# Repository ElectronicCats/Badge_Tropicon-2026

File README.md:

# Badge Tropicon 2026

Badge Oficial de Trpicon 2026

## Hardware
- ESP32-C6
- AHT30
- SI4463
- VGdd79S915N0S1
- Wide Angle 2.79 inch 142x428 Color IPS TFT Display NV3007 Controller

## Tecnologia
- LoRa
- WIFi
- BLE
- Zigbee
- Thread
- [AIS](https://es.wikipedia.org/wiki/Sistema_de_Identificaci%C3%B3n_Autom%C3%A1tica)
- [meshtastic](https://github.com/meshtastic)

<div align="center" markdown="1">

<h1>Tropicon 2026 — Firmware</h1>

Firmware personalizado de Meshtastic para el badge del evento **Tropicon 2026**, desarrollado por **Electronic Cats**. Incluye integración de agenda de pláticas, talleres, monitor AIS de embarcaciones, telemetría ambiental y mensajería LoRa.

</div>

## Primeros pasos
> [!IMPORTANT]
> INSTRUCCIONES COMPLETAS DE USO

Dirigete al [Repositorio de Fimrware](https://github.com/ElectronicCats/Tropicon-2026_Firmware) para instrucciones completas de uso

## Botones y navegación general

El badge cuenta con cuatro botones físicos:

| Botón | Pulsación corta | Pulsación larga (~1 s) |
|-------|----------------|------------------------|
| **UP** | Pantalla anterior / Ítem anterior | Abrir menú de acciones de la pantalla actual |
| **DOWN** | Pantalla siguiente / Ítem siguiente | — |
| **LEFT** | Izquierda / Día anterior (en Talks) | — |
| **RIGHT** | Derecha / Siguiente stage (en Talks) | — |

> [!TIP]
> El **botón UP largo** es la acción principal de cada pantalla. Desde cualquier pantalla, úsalo para acceder a las opciones disponibles: enviar mensajes, navegar a la agenda, configurar LoRa, etc.

---

## Pantallas del dispositivo

Navega entre pantallas con **UP** (anterior) y **DOWN** (siguiente). El ciclo completo es:

| # | Pantalla | Descripción |
|---|----------|-------------|
| 1 | **Talks** | Agenda de pláticas y talleres de Tropicon 2026 |
| 2 | **AIS** | Monitor de embarcaciones (Automatic Identification System) |
| 3 | **Clock** | Reloj digital o analógico |
| 4 | **Home** | Estado del nodo: nombre, batería y canal LoRa |
| 5 | **Messages** | Mensajes de texto recibidos y enviados en la malla LoRa |
| 6 | **Node List** | Lista de nodos detectados en la malla |
| 7 | **Telemetry** | Métricas del entorno: Temperatura y Humedad (sensor AHT10) |
| 8 | **GPS** | Brújula y coordenadas (deshabilitado — sin módulo GPS) |
| 9 | **LoRa** | Estadísticas de radio: SNR, RSSI y frecuencia |
| 10 | **System** | Información de sistema: uptime y memoria libre |

---

## Menú de Acciones (Home Action)

Desde la pantalla **Home**, presiona **UP largo** para abrir el menú *"Home Action"*:

| Opción | Qué hace |
|--------|----------|
| **Back** | Cierra el menú sin cambios |
| **Sleep Screen** | Apaga la pantalla para ahorrar batería (cualquier botón la reactiva) |
| **Talks** | Abre directamente la agenda de pláticas y talleres |

---

## Agenda de Pláticas y Talleres (Talks)

La agenda carga automáticamente los datos desde la flash del dispositivo:

| Archivo | Contenido |
|---------|-----------|
| `/schedule.json` | Pláticas principales (Track 1 y Track Villas) |
| `/talleres.json` | Talleres simultáneos (Salón Maya, La Isla, Suite 1, Suite 2) |

Para acceder a la agenda puedes:
- Navegar con **UP/DOWN** hasta llegar a la pantalla **Talks**, o
- Desde cualquier pantalla, abrir el menú con **UP largo** y seleccionar **Talks**.

### Vista lista

Muestra el listado de pláticas del día y stage (escenario) actualmente seleccionados. El encabezado indica `Día — Stage`.

| Acción | Resultado |
|--------|-----------|
| **UP** corto | Sube al ítem anterior de la lista |
| **UP** corto (en la primera plática) | Sale de la agenda y regresa al menú principal |
| **DOWN** | Baja al ítem siguiente de la lista |
| **LEFT** | Cambia al día anterior (cíclico); resetea el stage y la selección |
| **RIGHT** | Avanza al siguiente stage; si ya es el último stage, avanza al siguiente día |
| **UP largo** | Entra a la **vista detalle** de la plática seleccionada |

> [!TIP]
> Para **salir de la agenda en cualquier momento**, presiona **UP** cuando estés en la primera plática de la lista — el badge regresará automáticamente al menú principal de pantallas.

### Vista detalle

Muestra el título completo, nombre del ponente, horario, sala, imagen del ponente y el marcador de interés actual.

| Acción | Resultado |
|--------|-----------|
| **UP** corto | Regresa a la vista lista |
| **DOWN** | Avanza a la siguiente plática (permanece en vista detalle) |
| **LEFT** | Retrocede a la plática anterior (cambia de stage/día si es necesario) |
| **RIGHT** | Avanza a la plática siguiente (cambia de stage/día si es necesario) |
| **UP largo** | Cicla el estado de interés: `Sin interés → Asistir → Tal vez → Saltar` |

### Marcadores de interés y notificaciones

Los marcadores se muestran en la esquina superior derecha de cada plática en la vista lista:

| Marcador | Estado | Descripción |
|----------|--------|-------------|
| _(vacío)_ | Sin interés | Sin acción |
| `[A]` | **Asistir** | El badge enviará una notificación a tu app Meshtastic 10 minutos antes de que comience |
| `[T]` | **Tal vez** | Recordatorio opcional |
| `[S]` | **Saltar** | Marcado para no asistir |

> [!IMPORTANT]
> Los marcadores se guardan automáticamente en la flash del dispositivo y **persisten entre reinicios**. Si tienes el badge conectado a la app Meshtastic y una plática marcada como `[A]` (Asistir) está por comenzar, recibirás una notificación push en tu teléfono con el mensaje _"Tropicon: [nombre de plática] empieza en 10 min"_.

---

## Monitor AIS de Embarcaciones

La pantalla **AIS** recibe y decodifica señales VHF del sistema de identificación automática de embarcaciones (AIS), usado internacionalmente por barcos para reportar su posición y datos.

Para acceder, navega con **UP/DOWN** hasta la pantalla **AIS**.

### Información mostrada

La pantalla se divide en:

- **Encabezado**: muestra el canal AIS activo (`ch A` o `ch B`, es decir canal 87B o 88B) y el total de tramas recibidas (`frm`).
- **Lista de embarcaciones** (ordenadas de más reciente a más antigua): cada fila contiene:
  - **MMSI**: identificador único de la embarcación (9 dígitos)
  - **RSSI**: nivel de señal recibida en dBm
  - **Antigüedad**: tiempo desde la última trama recibida (en segundos, o `>1h`)
  - **Tipo de mensaje**: badge `T1`, `T2`, etc. (tipo de trama AIS)
  - **Sentencia NMEA**: frase AIS cruda recibida (truncada para caber en pantalla)

Cuando no se han recibido embarcaciones, la pantalla muestra `Listening...` indicando que el receptor está activo y esperando señales.

> [!NOTE]
> El AIS trabaja en frecuencias VHF (~162 MHz). La recepción depende de la proximidad a cuerpos de agua navegables y de la línea de visión con las embarcaciones.

---

## Mensajes — Recibir y Enviar

La pantalla **Messages** muestra todos los mensajes de texto intercambiados en la malla LoRa, presentados en formato de burbuja (mensajes propios a la derecha, mensajes recibidos a la izquierda).

### Navegar a la pantalla de mensajes

Usa **RIGHT/LEFT** desde cualquier pantalla hasta llegar a **Messages**.

### Ver mensajes

- Cada mensaje muestra: remitente, tiempo transcurrido, canal o DM, y el texto.
- Los mensajes propios muestran un indicador de estado de entrega:
  - Palomita `✓` — mensaje confirmado (ACK del destino)
  - `✗` — falla o tiempo de espera agotado
  - Círculo — reenviado por un nodo relay

### Enviar un mensaje (nuevo)

1. Navega a la pantalla **Messages**.
2. Presiona **UP largo** para abrir el menú *"Message Action"*.
3. Selecciona **Reply** → **With Preset** para elegir un mensaje predefinido de la lista.
4. Usa **RIGHT/LEFT** para seleccionar el mensaje deseado y **UP largo** para enviarlo.

> [!NOTE]
> La opción **With Freetext** (teclado libre) solo aparece si se detecta un teclado externo conectado al badge.

### Responder a un mensaje recibido

1. Navega a la pantalla **Messages** donde aparece el mensaje.
2. Presiona **UP largo** para abrir *"Message Action"*.
3. Selecciona **Reply** y elige:
   - **With Preset** — selecciona una respuesta de la lista de mensajes predefinidos.
   - **With Freetext** — escribe tu propio texto (requiere teclado externo).

### Otras opciones del menú Message Action

| Opción | Qué hace |
|--------|----------|
| **Back** | Cierra el menú |
| **Reply** | Abre el submenú para responder |
| **View Chats** | Cambia el filtro de vista: todos los mensajes, por canal o por conversación directa |
| **Mute Channel** / **Unmute Channel** | Silencia o reactiva las notificaciones del canal actual |
| **Delete** | Elimina mensajes (el más antiguo, el actual o todos) |

---

## Telemetría del Entorno

La pantalla **Telemetry** muestra las métricas ambientales medidas en tiempo real por el sensor **AHT10** integrado en el badge:

- **Temperatura** en grados Celsius
- **Humedad relativa** en porcentaje (%)

Para acceder, navega con **UP/DOWN** hasta llegar a la pantalla **Telemetry**.

Las métricas se actualizan automáticamente cada segundo. El badge también transmite estos datos periódicamente por la malla LoRa para que otros nodos y la app Meshtastic puedan visualizarlos.

---

### Recursos útiles

- [Documentación oficial de Meshtastic](https://meshtastic.org/docs/) — arquitectura, módulos, protocolo LoRa y API.
- [Repositorio base de Meshtastic firmware](https://github.com/meshtastic/firmware) — código fuente upstream del que se deriva este firmware.
- [Documentación de PlatformIO](https://docs.platformio.org/) — comandos de compilación, ambientes y gestión de librerías.
- [Foro de la comunidad Meshtastic](https://meshtastic.discourse.group/) — preguntas, proyectos y soporte comunitario.
- [Electronic Cats en GitHub](https://github.com/ElectronicCats) — otros proyectos de hardware y firmware de Electronic Cats.

## Credits

Designed and developed by the **Electronic Cats** firmware and hardware team.

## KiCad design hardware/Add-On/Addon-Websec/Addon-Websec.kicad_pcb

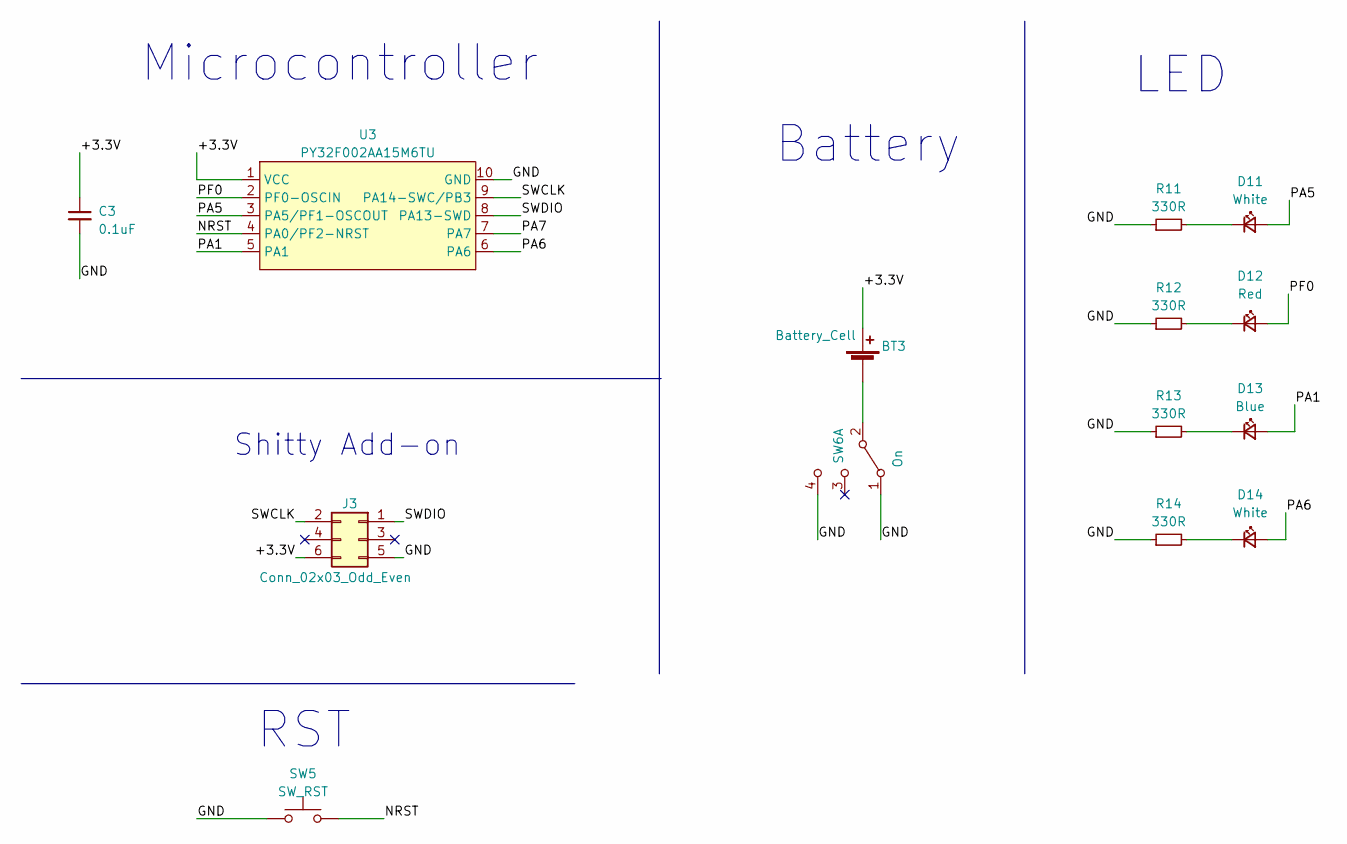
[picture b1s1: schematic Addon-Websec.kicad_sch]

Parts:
BT3: Battery_Cell; BAT-HLD-001; LCSC# C964833
C3: 0.1uF; C_0805_2012Metric; LCSC# C235731
D11, D14: White; LED_0805_2012Metric; LCSC# C84258
D12: Red; LED_0805_2012Metric; LCSC# C965812
D13: Blue; LED_0805_2012Metric; LCSC# C205441
J3: Conn_02x03_Odd_Even; B-2100N06P-B111_CKM; LCSC# C124390
R11, R12, R13, R14: 330R; R_0805_2012Metric; LCSC# C119075
SW5: SW_RST; SW_SPST_TL3342; LCSC# C318889
SW6: On; MSK12C02; LCSC# C431540
U3: PY32F002AA15M6TU; PY32F002AA15M; LCSC# C5292058

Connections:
/+3.3V: BT3.2 (+), C3.1, J3.6, U3.1 (VCC)
/GND: C3.2, J3.5, R11.1, R12.1, R13.1, R14.1, SW5.1, SW6.1 (A), SW6.4 (C), U3.10 (GND)
/NRST: SW5.2, U3.4 (PA0/PF2-NRST)
/PA1: D13.2 (A), U3.5 (PA1)
/PA5: D11.2 (A), U3.3 (PA5/PF1-OSCOUT)
/PA6: D14.2 (A), U3.6 (PA6)
/PA7: U3.7 (PA7)
/PF0: D12.2 (A), U3.2 (PF0-OSCIN)
/SWCLK: J3.2, U3.9 (PA14-SWC/PB3)
/SWDIO: J3.1, U3.8 (PA13-SWD)
unnamed: BT3.1 (-), SW6.2 (B)
unnamed: D11.1 (K), R11.2
unnamed: D12.1 (K), R12.2
unnamed: D13.1 (K), R13.2
unnamed: D14.1 (K), R14.2

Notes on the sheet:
Battery
RST
Microcontroller
Shitty Add-on
LED

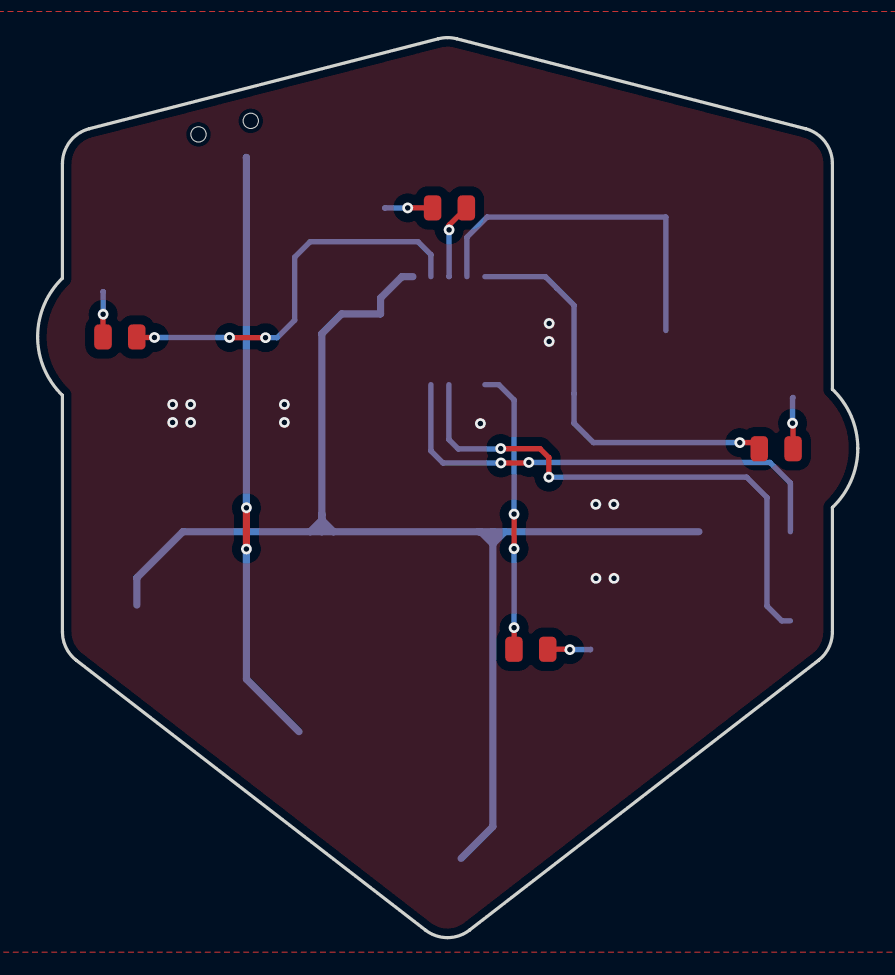
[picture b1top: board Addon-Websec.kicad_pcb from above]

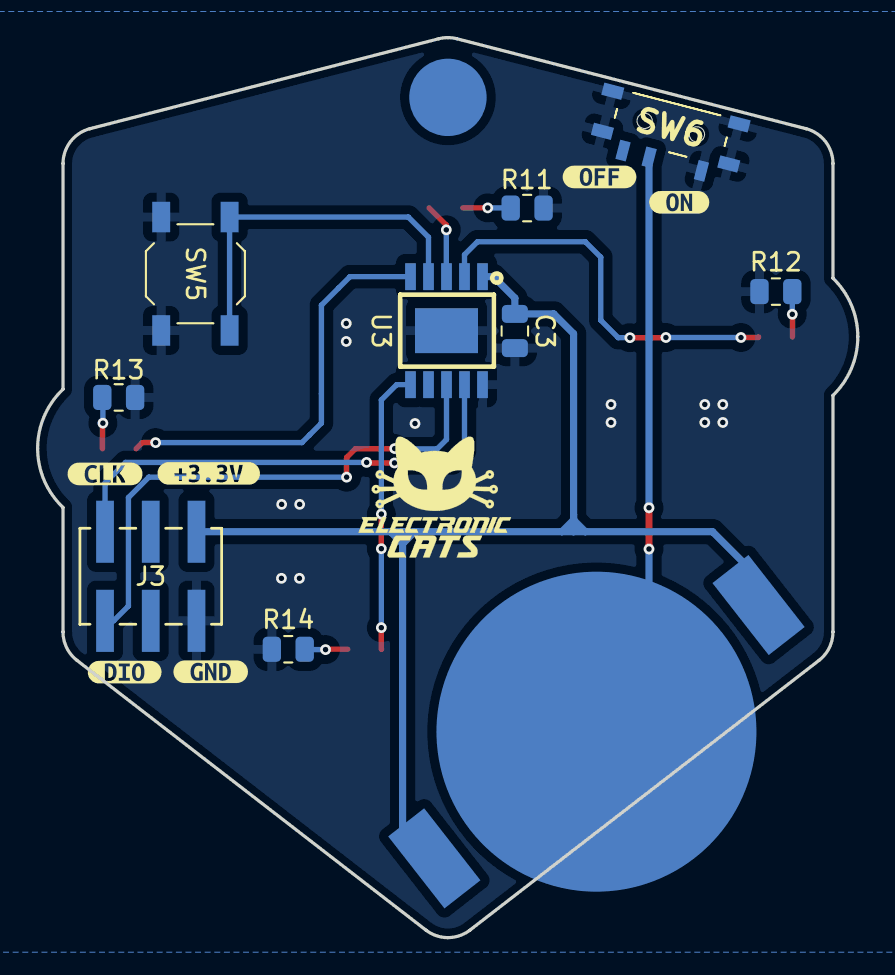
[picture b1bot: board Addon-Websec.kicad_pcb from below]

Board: 2 copper layers, 45.6 x 50.0 mm, 20 parts (16 on the bottom side), 14 nets.

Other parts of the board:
kibuzzard-66EC9C8E: G***; kibuzzard-66EC9C8E
kibuzzard-66EC9CA5: G***; kibuzzard-66EC9CA5
kibuzzard-66EC9D2A: G***; kibuzzard-66EC9D2A
kibuzzard-66EC9DE2: G***; kibuzzard-66EC9DE2
kibuzzard-66ECA9F9: G***; kibuzzard-66ECA9F9
kibuzzard-66ECAA39: G***; kibuzzard-66ECAA39

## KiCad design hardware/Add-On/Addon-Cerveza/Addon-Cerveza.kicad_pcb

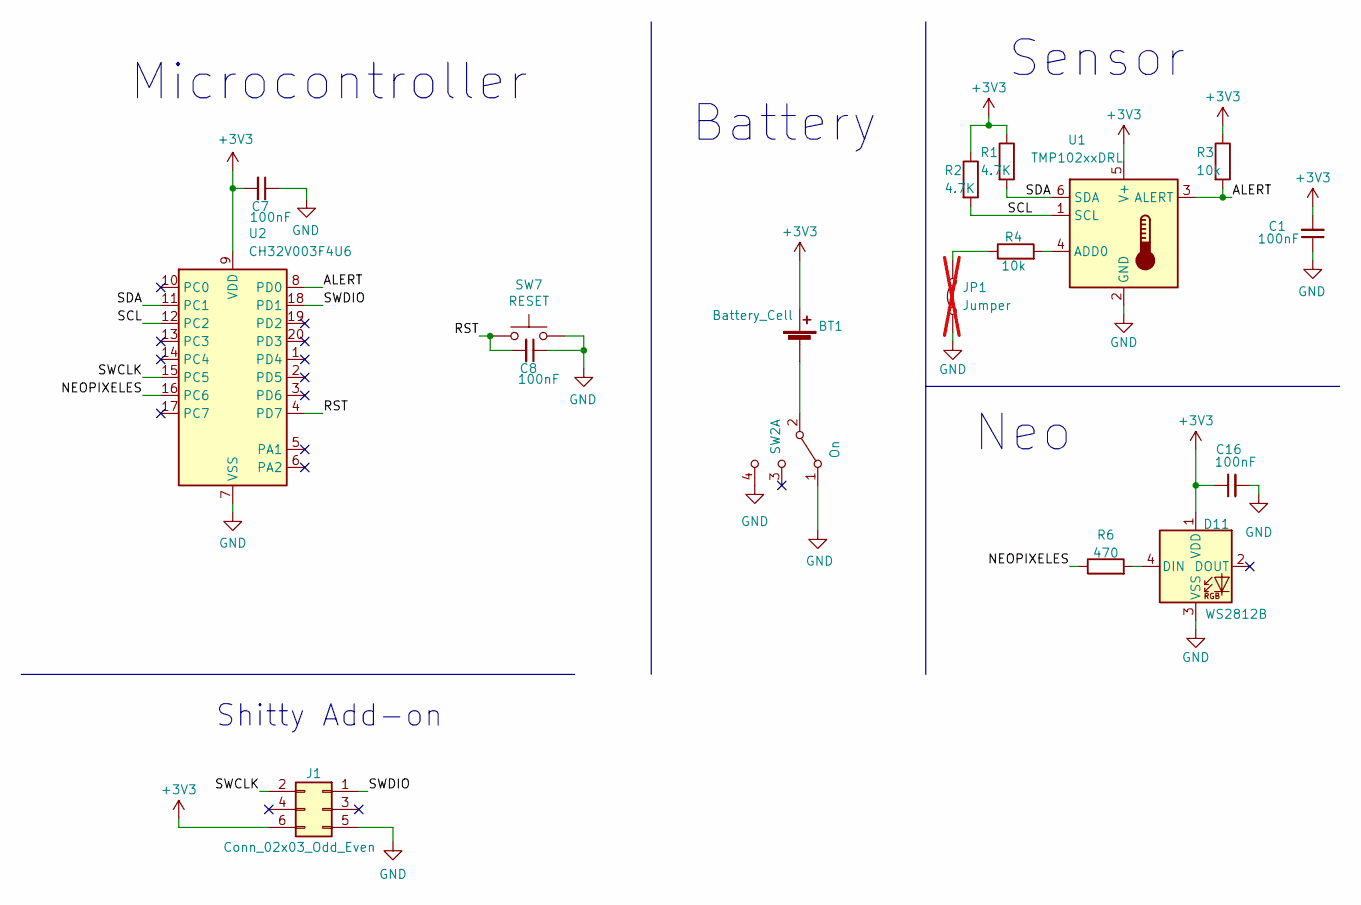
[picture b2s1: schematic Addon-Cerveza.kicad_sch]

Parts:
BT1: Battery_Cell; BAT-HLD-001; LCSC# C964833
C1, C7, C8, C16: 100nF; C_0603_1608Metric; LCSC# C478888
D11: WS2812B; LED_SK6812-E; LCSC# C5378731
J1: Conn_02x03_Odd_Even; B-2100N06P-B111_CKM; LCSC# C124390
JP1: Jumper; SolderJumper-2_P1.3mm_Bridged_RoundedPad1.0x1.5mm; not fitted
R1, R2: 4.7K; R_0603_1608Metric; LCSC# C2907034
R3, R4: 10k; R_0603_1608Metric; LCSC# C2930027
R6: 470; R_0603_1608Metric; LCSC# C2907172
SW2: On; MSK12C02; LCSC# C431540
SW7: RESET; SW_SPST_TL3342; LCSC# C318889
U1: TMP102xxDRL; SOT-563; LCSC# C5692997
U2: CH32V003F4U6; TSSOP-20_4.4x6.5mm_P0.65mm; LCSC# C5187096

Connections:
+3V3: BT1.2 (+), C1.2, C7.2, C16.1, D11.1 (VDD), J1.6, R1.1, R2.1, R3.1, U1.5 (V+), U2.9 (VDD)
/ALERT: R3.2, U1.3 (ALERT), U2.8 (PD0)
/NEOPIXELES: R6.1, U2.16 (PC6)
/RST: C8.2, SW7.2, U2.4 (PD7)
/SCL: R2.2, U1.1 (SCL), U2.12 (PC2)
/SDA: R1.2, U1.6 (SDA), U2.11 (PC1)
/SWCLK: J1.2, U2.15 (PC5)
/SWDIO: J1.1, U2.18 (PD1)
GND: C1.1, C7.1, C8.1, C16.2, D11.3 (VSS), J1.5, JP1.1 (A), SW2.1 (A), SW2.4 (C), SW7.1, U1.2 (GND), U2.7 (VSS)
unnamed: BT1.1 (-), SW2.2 (B)
unnamed: D11.4 (DIN), R6.2
unnamed: JP1.2 (B), R4.1
unnamed: R4.2, U1.4 (ADD0)

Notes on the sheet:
Shitty Add-on
Battery
Neo
Microcontroller
Sensor

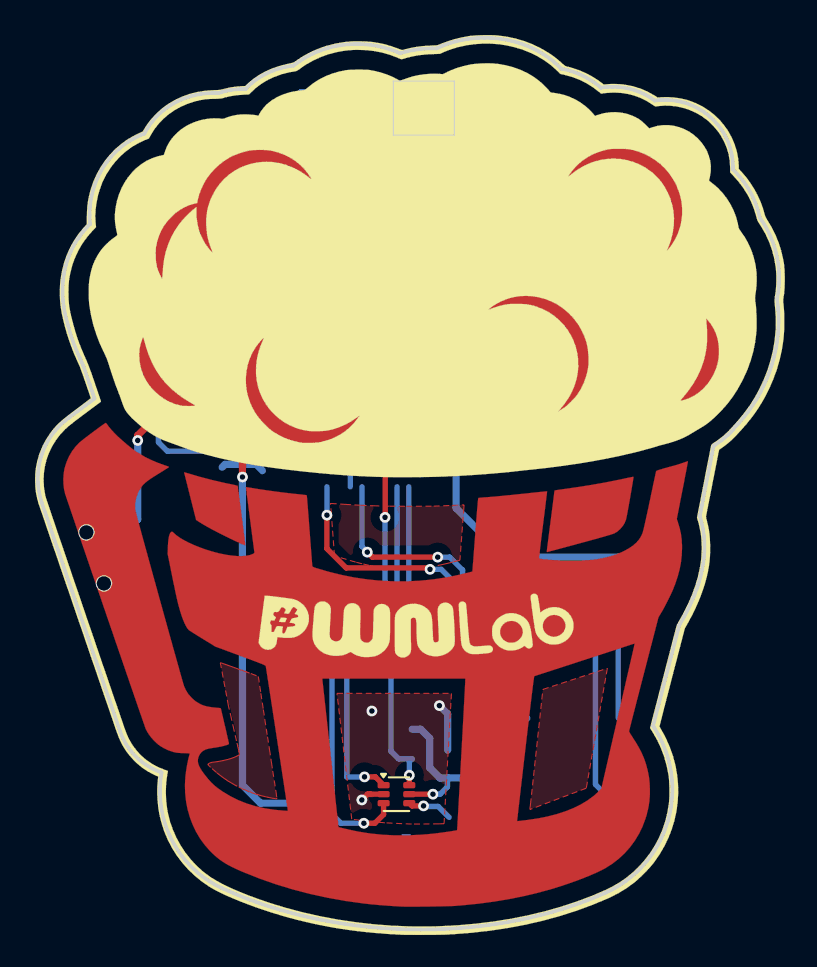
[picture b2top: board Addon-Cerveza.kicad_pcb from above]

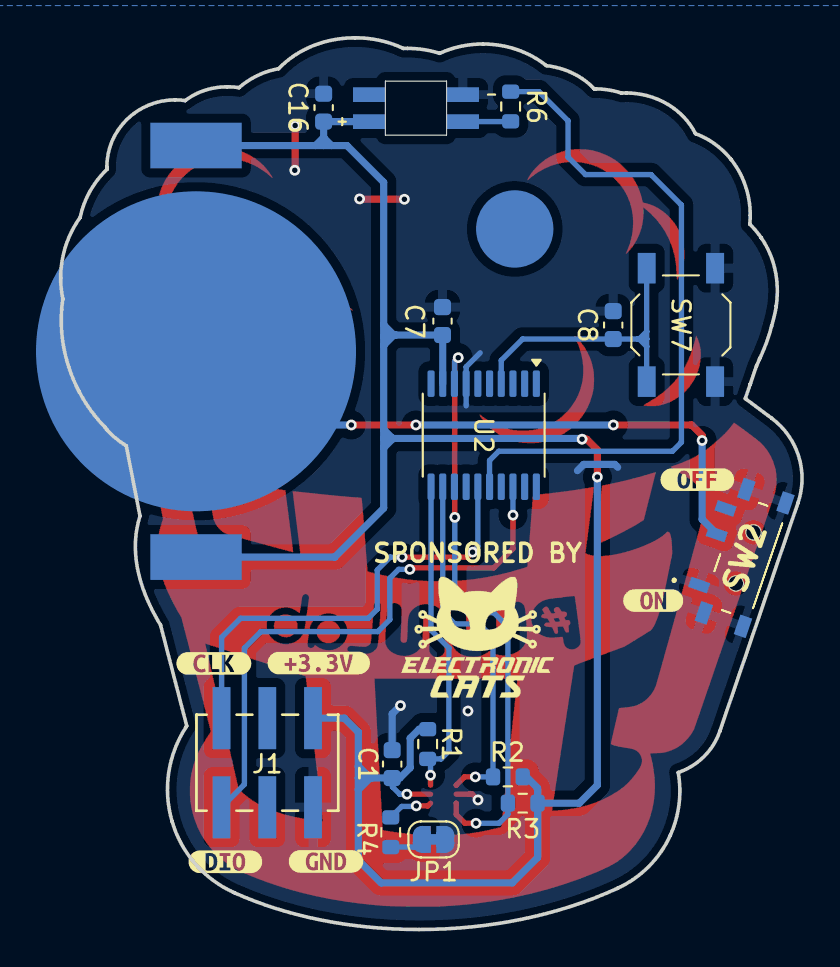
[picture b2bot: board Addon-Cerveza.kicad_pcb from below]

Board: 2 copper layers, 41.2 x 49.5 mm, 24 parts (22 on the bottom side), 13 nets.

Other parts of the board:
Ref**: Val**; Tarrito de cerveza_Add-On_NV
kibuzzard-66EC9C8E: G***; kibuzzard-66EC9C8E
kibuzzard-66EC9CA5: G***; kibuzzard-66EC9CA5
kibuzzard-66EC9D2A: G***; kibuzzard-66EC9D2A
kibuzzard-66EC9DE2: G***; kibuzzard-66EC9DE2
kibuzzard-66ECA9F9: G***; kibuzzard-66ECA9F9
kibuzzard-66ECAA39: G***; kibuzzard-66ECAA39

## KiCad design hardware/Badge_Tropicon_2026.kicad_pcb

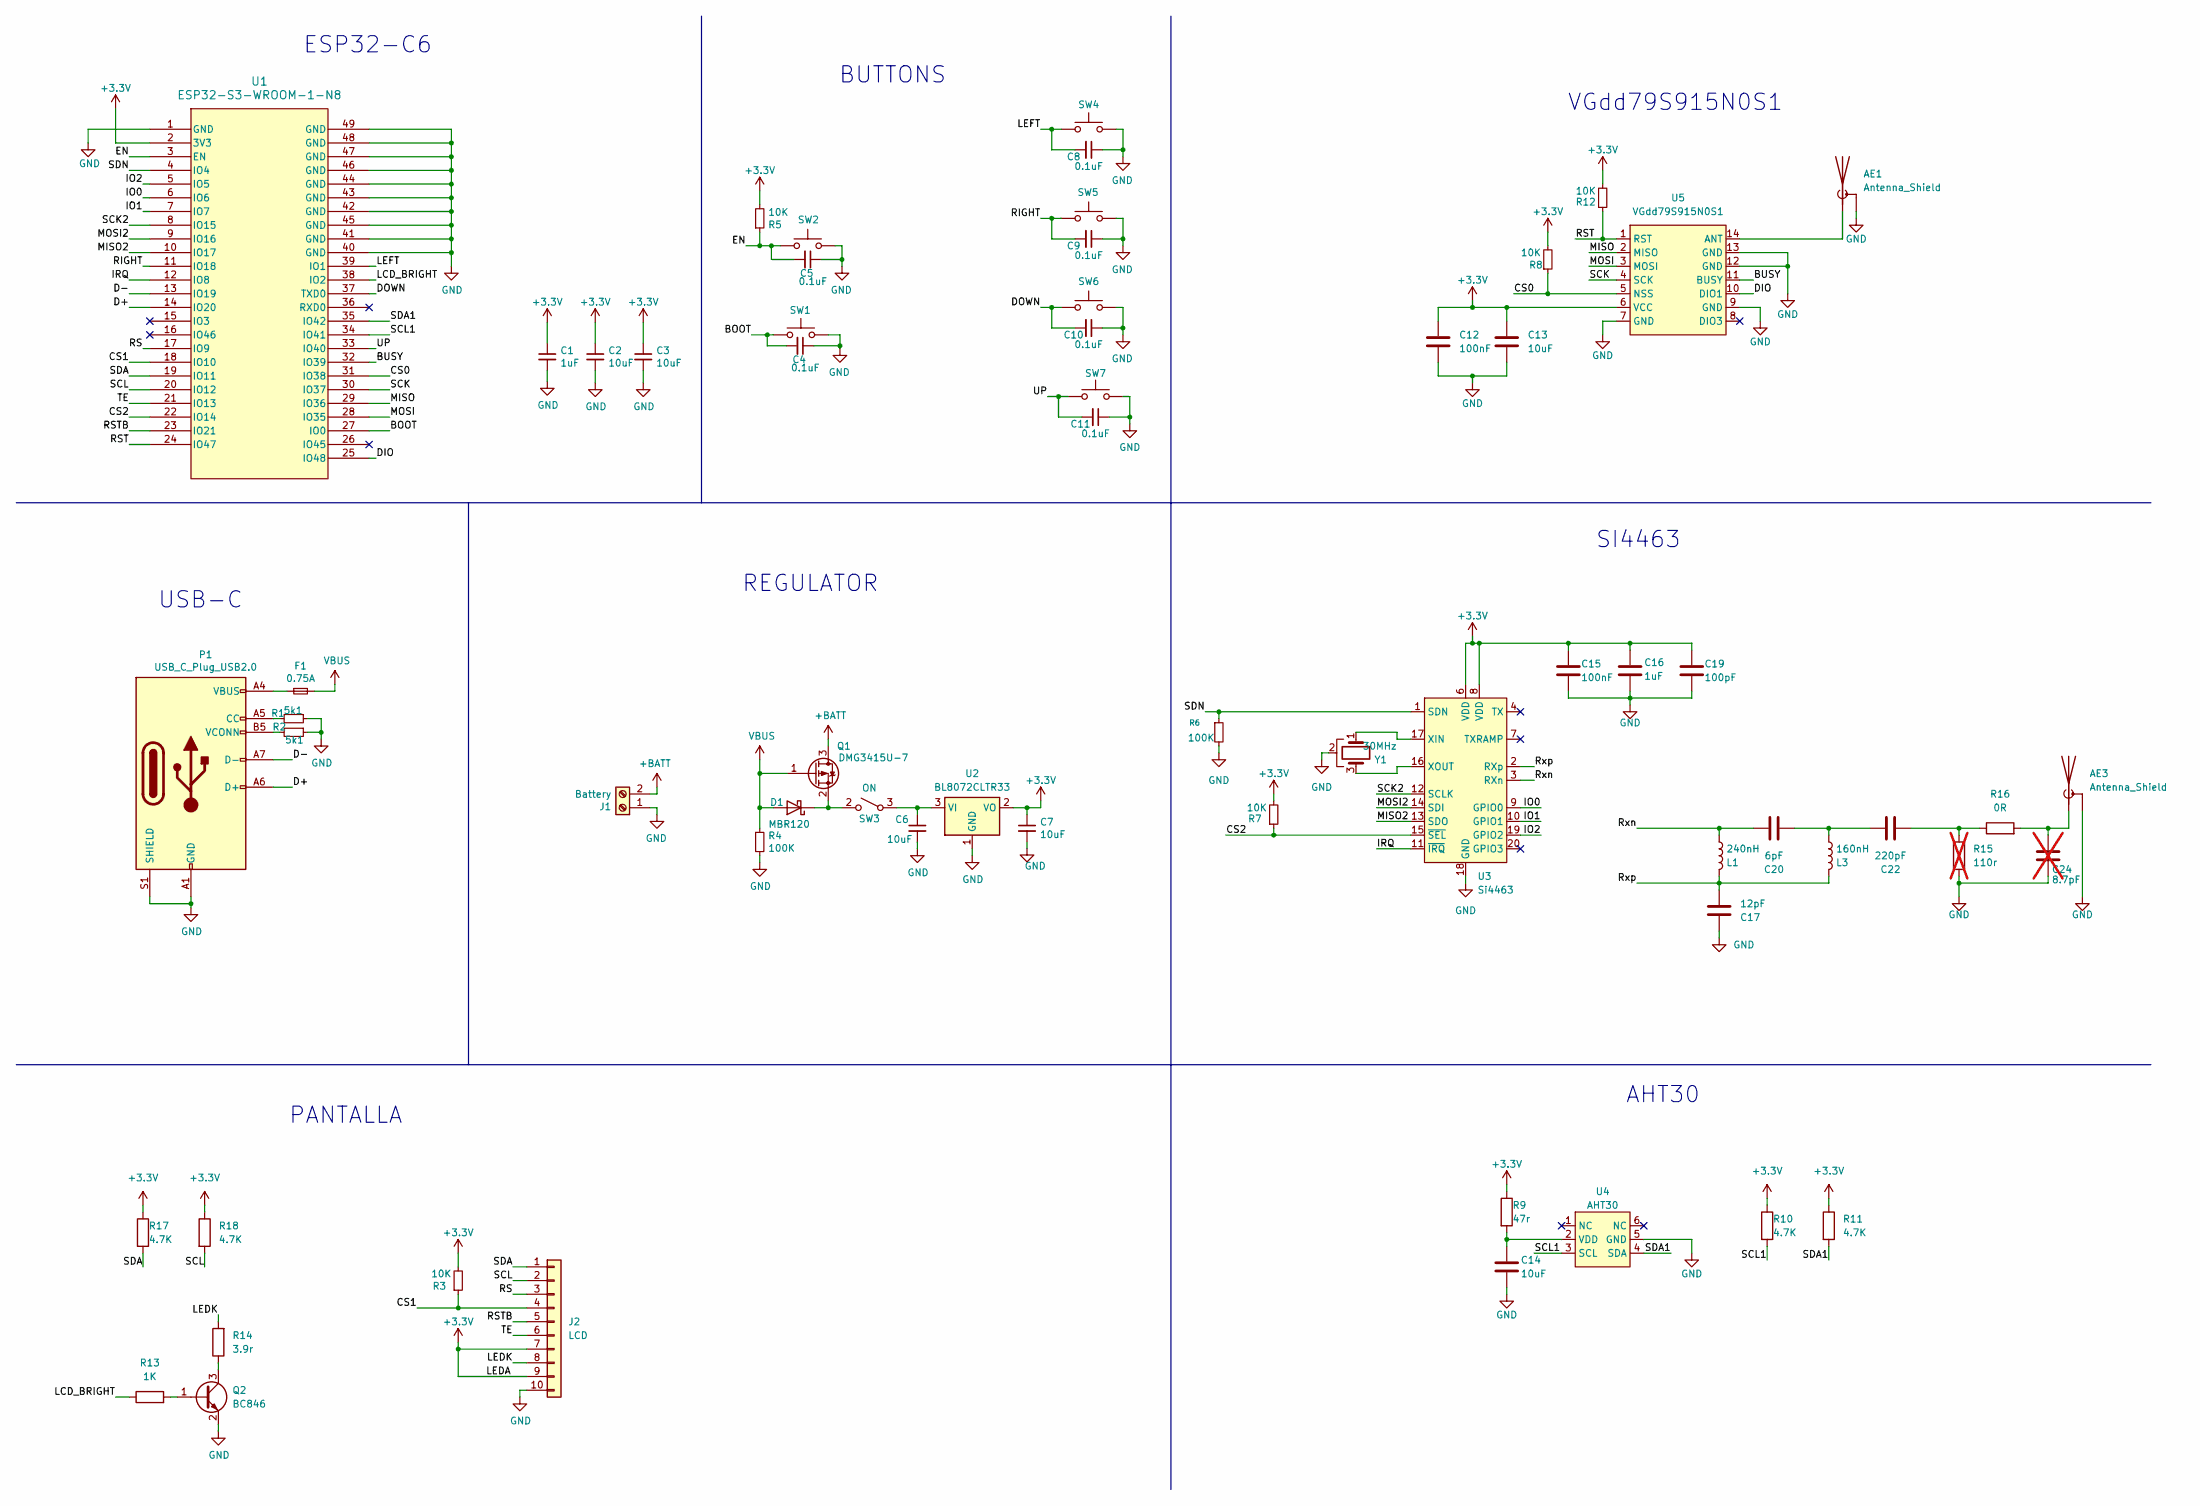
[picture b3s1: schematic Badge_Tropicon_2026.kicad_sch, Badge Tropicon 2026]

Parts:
AE1: Antenna_Shield; SMA_EDGE; LCSC# C530661
AE3: Antenna_Shield; PinHeader_1x02_P2.54mm_Vertical
C1, C16: 1uF; C_0603_1608Metric; LCSC# C15849
C2, C3, C6, C7, C13, C14: 10uF; C_0603_1608Metric; LCSC# C85713
C4, C5, C8, C9, C10, C11: 0.1uF; C_0603_1608Metric; LCSC# C478888
C12, C15: 100nF; C_0603_1608Metric; LCSC# C14663
C17: 12pF; C_0603_1608Metric; LCSC# C2241577
C19: 100pF; C_0603_1608Metric; LCSC# C7503509
C20: 6pF; C_0603_1608Metric; LCSC# C41361249
C22: 220pF; C_0603_1608Metric; LCSC# C519500
C24: 8.7pF; C_0603_1608Metric; LCSC# C5186907; not fitted
D1: MBR120; D_SOD-123F; LCSC# C130880
F1: 0.75A; Fuse_0603_1608Metric; LCSC# C182438
J1: Battery; BAT-TH_BH-AAA-A1AJ024; LCSC# C5290193
J2: LCD; Hirose_FH12-10S-0.5SH_1x10-1MP_P0.50mm_Horizontal; LCSC# C262583
L1: 240nH; L_0603_1608Metric; LCSC# C668512
L3: 160nH; L_0603_1608Metric; LCSC# C434822
P1: USB_C_Plug_USB2.0; C393939; LCSC# C393939
Q1: DMG3415U-7; SOT-23; LCSC# C96616
Q2: BC846; SOT-23; LCSC# C49238181
R1, R2: 5k1; R_0603_1608Metric; LCSC# C113390
R3, R5, R7, R8, R12: 10K; R_0603_1608Metric; LCSC# C2930027
R4, R6: 100K; R_0603_1608Metric; LCSC# C25803
R9: 47r; R_0603_1608Metric; LCSC# C23182
R10, R11, R17, R18: 4.7K; R_0603_1608Metric; LCSC# C2907034
R13: 1K; R_0603_1608Metric; LCSC# C2907002
R14: 3.9r; R_0603_1608Metric; LCSC# C2933216
R15: 110r; C_0603_1608Metric; LCSC# C2906985; not fitted
R16: 0R; C_0603_1608Metric; LCSC# C2906974
SW1, SW2, SW4, SW5, SW6, SW7: SW_SPST_TL3342; LCSC# C318889
SW3: ON; MSK12C02; LCSC# C431540
U1: ESP32-S3-WROOM-1-N8; ESP32-S3-WROOM-1_EXP
U2: BL8072CLTR33; SOT-223; LCSC# C843780
U3: Si4463; QFN-20-1EP_4x4mm_P0.5mm_EP2.6x2.6mm_ThermalVias; LCSC# C476202
U4: AHT30; LCSC# C45354925
U5: VGdd79S915N0S1; LCSC# C2848401
Y1: 30MHz; Crystal_SMD_Abracon_ABM8G-4Pin_3.2x2.5mm; LCSC# C29538

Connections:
+3.3V: C1.1, C2.1, C3.1, C7.1, C12.1, C13.1, C15.1, C16.1, C19.1, J2.7, J2.9, R3.2, R5.2, R7.2, R8.2, R9.1, R10.1, R11.1, R12.2, R17.1, R18.1, U1.2 (3V3), U2.2 (VO), U3.6 (VDD), U3.8 (VDD), U5.6 (VCC)
+BATT: J1.2, Q1.3 (D)
/BOOT: C4.2, SW1.2, U1.27 (IO0)
/BUSY: U1.32 (IO39), U5.11 (BUSY)
/CS0: R8.1, U1.31 (IO38), U5.5 (NSS)
/CS1: J2.4, R3.1, U1.18 (IO10)
/CS2: R7.1, U1.22 (IO14), U3.15 (~SEL)
/D+: P1.A6 (D+), U1.14 (IO20)
/D-: P1.A7 (D-), U1.13 (IO19)
/DIO: U1.25 (IO48), U5.10 (DIO1)
/DOWN: C10.2, SW6.2, U1.37 (TXD0)
/EN: C5.2, R5.1, SW2.2, U1.3 (EN)
/IO0: U1.6 (IO6), U3.9 (GPIO0)
/IO1: U1.7 (IO7), U3.10 (GPIO1)
/IO2: U1.5 (IO5), U3.19 (GPIO2)
/IRQ: U1.12 (IO8), U3.11 (~IRQ)
/LCD_BRIGHT: R13.1, U1.38 (IO2)
/LEDK: J2.8, R14.2
/LEFT: C8.2, SW4.2, U1.39 (IO1)
/MISO: U1.29 (IO36), U5.2 (MISO)
/MISO2: U1.10 (IO17), U3.13 (SDO)
/MOSI: U1.28 (IO35), U5.3 (MOSI)
/MOSI2: U1.9 (IO16), U3.14 (SDI)
/RIGHT: C9.2, SW5.2, U1.11 (IO18)
/RS: J2.3, U1.17 (IO9)
/RST: R12.1, U1.24 (IO47), U5.1 (RST)
/RSTB: J2.5, U1.23 (IO21)
/Rxn: C20.1, L1.2, U3.3 (RXn)
/Rxp: C17.2, L1.1, L3.1, U3.2 (RXp)
/SCK: U1.30 (IO37), U5.4 (SCK)
/SCK2: U1.8 (IO15), U3.12 (SCLK)
/SCL: J2.2, R18.2, U1.20 (IO12)
/SCL1: R10.2, U1.34 (IO41), U4.3 (SCL)
/SDA: J2.1, R17.2, U1.19 (IO11)
/SDA1: R11.2, U1.35 (IO42), U4.4 (SDA)
/SDN: R6.1, U1.4 (IO4), U3.1 (SDN)
/TE: J2.6, U1.21 (IO13)
/UP: C11.2, SW7.2, U1.33 (IO40)
GND: AE1.2 (Shield), AE3.2 (Shield), C1.2, C2.2, C3.2, C4.1, C5.1, C6.2, C7.2, C8.1, C9.1, C10.1, C11.1, C12.2, C13.2, C14.2, C15.2, C16.2, C17.1, C19.2, C24.2, J1.1, J2.10, P1.A1 (GND), P1.A12 (GND), P1.B1 (GND), P1.B12 (GND), P1.S1 (SHIELD), Q2.2 (E), R1.1, R2.1, R4.2, R6.2, R15.2, SW1.1, SW2.1, SW4.1, SW5.1, SW6.1, SW7.1, U1.1 (GND), U1.40 (GND), U1.41 (GND), U1.42 (GND), U1.43 (GND), U1.44 (GND), U1.45 (GND), U1.46 (GND), U1.47 (GND), U1.48 (GND), U1.49 (GND), U2.1 (GND), U3.18 (GND), U3.21 (GND), U4.5 (GND), U5.7 (GND), U5.9 (GND), U5.12 (GND), U5.13 (GND), Y1.2, Y1.4
unnamed: AE1.1 (A), U5.14 (ANT)
unnamed: AE3.1 (A), C24.1, R16.2
unnamed: C20.2, C22.1, L3.2
unnamed: C22.2, R15.1, R16.1
unnamed: D1.1 (K), Q1.2 (S), SW3.2 (B)
unnamed: F1.1, P1.A4 (VBUS), P1.A9 (VBUS), P1.B4 (VBUS), P1.B9 (VBUS)
unnamed: P1.A5 (CC), R1.2
unnamed: P1.B5 (VCONN), R2.2
unnamed: Q2.1 (B), R13.2
unnamed: Q2.3 (C), R14.1
unnamed: C6.1, SW3.3 (A), U2.3 (VI)
unnamed: U3.17 (XIN), Y1.1
unnamed: U3.16 (XOUT), Y1.3
unnamed: C14.1, R9.2, U4.2 (VDD)
VBUS: D1.2 (A), F1.2, Q1.1 (G), R4.1

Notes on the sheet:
REGULATOR
BUTTONS
USB-C
VGdd79S915N0S1
ESP32-C6
SI4463
PANTALLA
AHT30

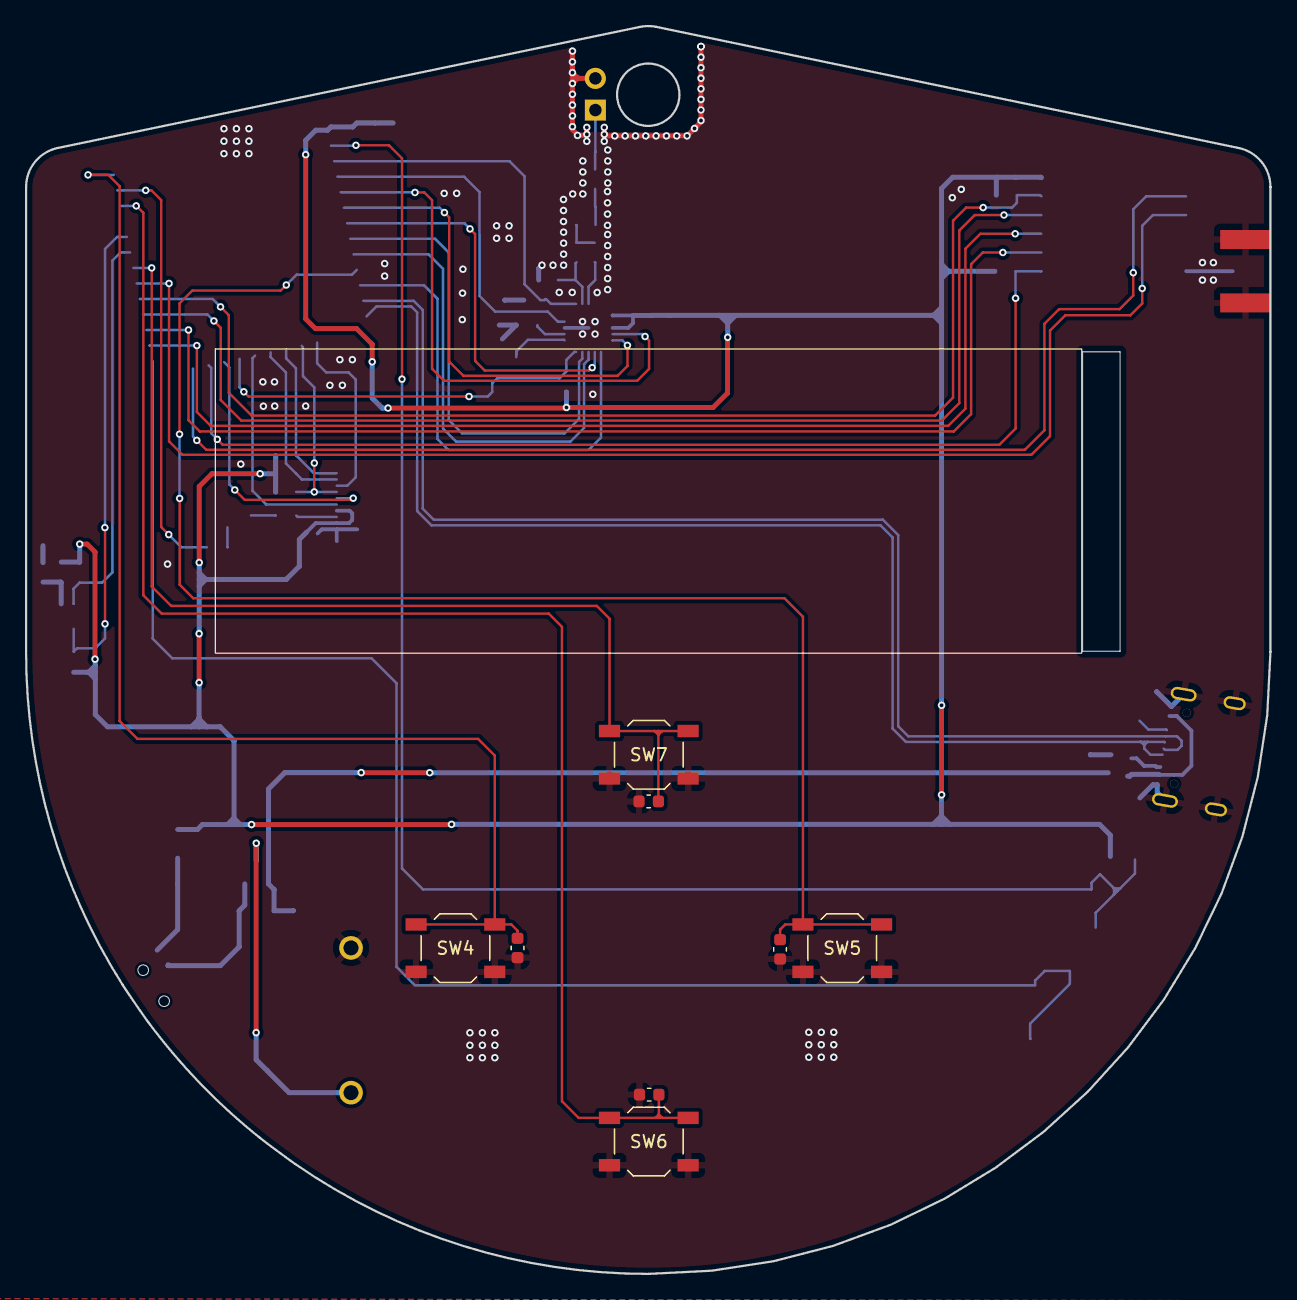
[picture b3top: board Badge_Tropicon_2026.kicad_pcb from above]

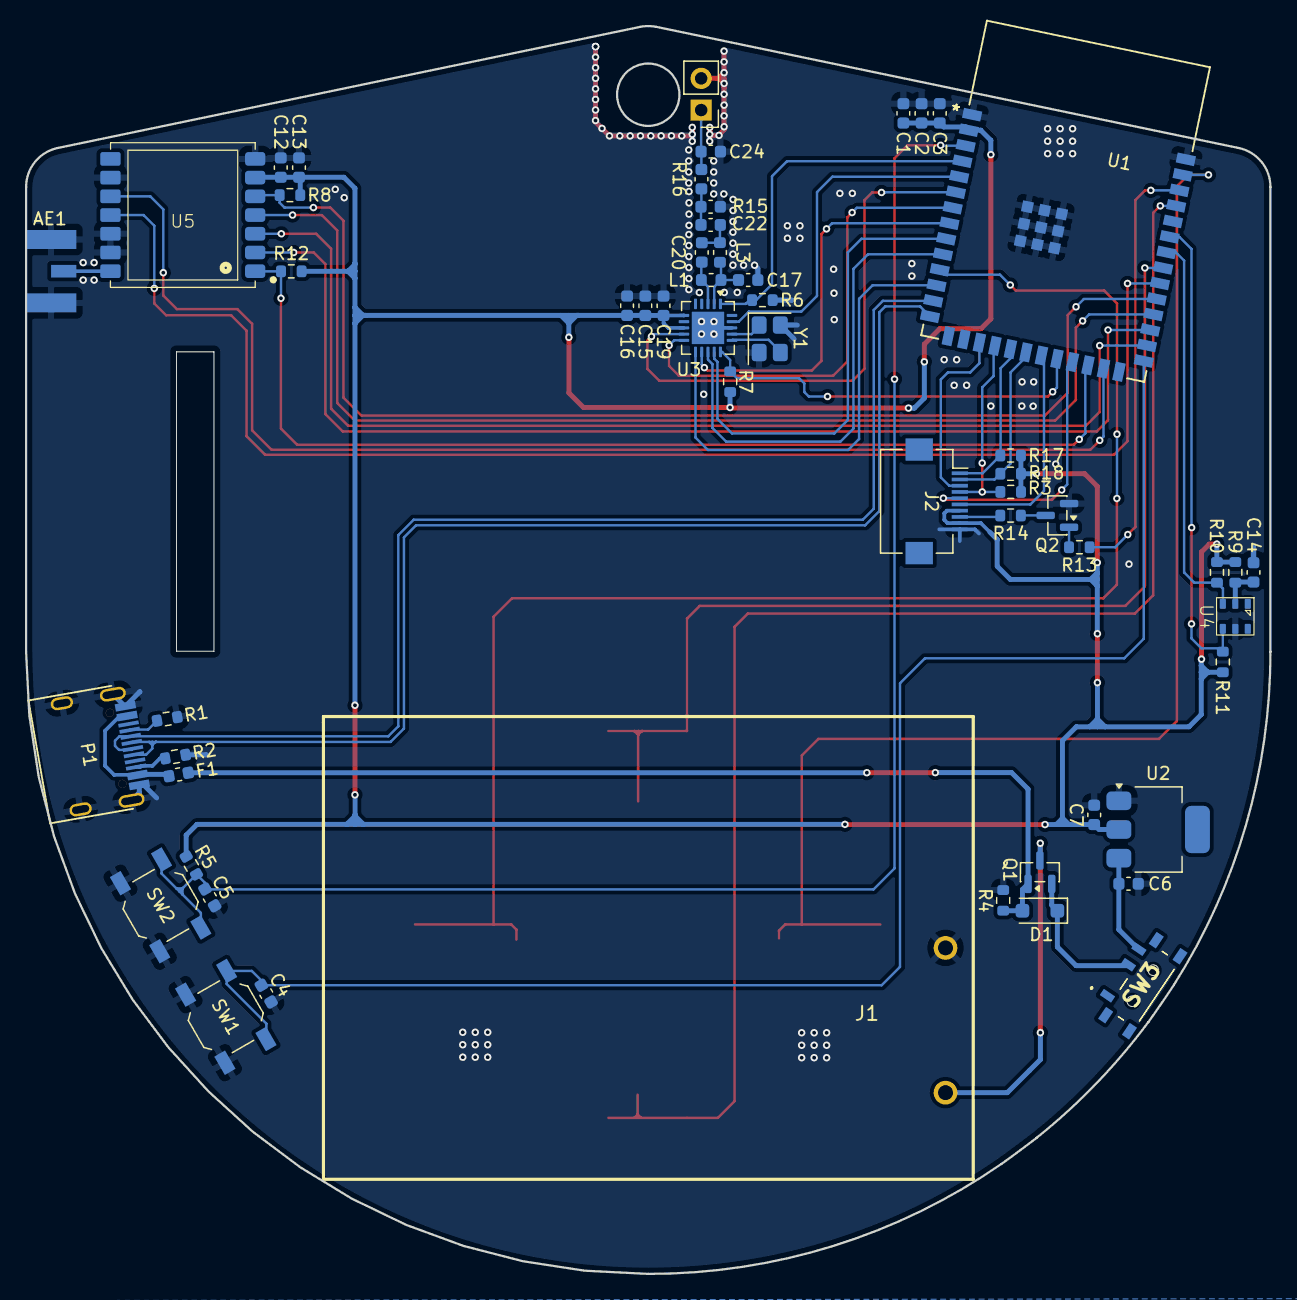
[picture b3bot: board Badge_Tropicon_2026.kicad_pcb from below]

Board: 2 copper layers, 99.7 x 100.0 mm, 63 parts (55 on the bottom side), 54 nets.

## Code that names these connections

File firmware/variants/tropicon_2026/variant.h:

#pragma once

// ══════════════════════════════════════════════════════════════════════════════
// variant.h — Custom hardware definition for ESP32-S3-WROOM-1-N8
// Board: Tropicon 2026
// Firmware: Meshtastic / PlatformIO
// ══════════════════════════════════════════════════════════════════════════════

// ── Hardware Identity ─────────────────────────────────────────────────────────
#define HW_VENDOR HardwareModel_PRIVATE_HW

// ── SX1262 LoRa — SPI Bus 1 ───────────────────────────────────────────────
// Meshtastic requires the SX126X_* prefix to properly initialize the radio,
// even if the module is an E22 variant.
#define USE_SX1262

#define SX126X_CS      38   // IO38 = CS0   (Chip Select)
#define SX126X_DIO1    48   // IO48 = DIO   (IRQ / DIO1)
#define SX126X_BUSY    39   // IO39 = BUSY  (Busy indicator)
#define SX126X_RESET   47   // IO47 = RST   (Reset, active low)

// SPI pins for SX1262 bus (VSPI / SPI Bus 1)
#define LORA_SCK       37   // IO37 = SCK
#define LORA_MISO      36   // IO36 = MISO
#define LORA_MOSI      35   // IO35 = MOSI

// TCXO: required for SX1262 E22 modules to prevent continuous reset loops.
#define SX126X_E22
// If SX126X_E22 causes issues, try setting the TCXO voltage directly instead:
// #define SX126X_DIO3_TCXO_VOLTAGE 1.8

// ── I2C Bus 1 — AHT30 Temperature & Humidity Sensor ──────────────────────────
#define I2C_SDA1       42   // IO42 = SDA1
#define I2C_SCL1       41   // IO41 = SCL1

// ── Display ER-TFT2.79-1 (controller: NV3007) — SPI Bus 2 (HSPI) ─────────────
//
// IMPORTANT — Interface clarification:
//   The NV3007 uses a 4-wire SPI interface exclusively (no I2C support).
//   The labels "SDA" and "SCL" in the module's FPC connector are the
//   manufacturer's own naming for the SPI data and clock lines respectively.
//   This is common practice in Chinese COG/COF display modules.
//
//   NV3007 pin  │ KiCad label │ ESP32-S3 pin │ SPI function
//   ────────────┼─────────────┼──────────────┼──────────────
//   SDA         │ SDA         │ IO11         │ MOSI (serial data in)
//   SCL         │ SCL         │ IO12         │ SCLK (serial clock)
//   D/CX        │ RS          │ IO09         │ Data/Command select
//   CSX         │ CS1         │ IO10         │ Chip Select (active low)
//   RESX        │ RSTB        │ IO21         │ Reset (active low)
//   TE          │ TE          │ IO13         │ Tearing Effect (frame sync)
//
//   There is NO MISO line in standard 4-wire SPI mode of the NV3007.
//
// NOTE on driver compatibility:
//   The NV3007 command set is NOT compatible with ST7789 / ILI9341.
//   A custom initialization sequence is required via TFT_eSPI User_Setup.h
//   or a dedicated NV3007 driver. Do NOT use USE_ST7789.

#define TFT_SPI_HOST   2    // HSPI (SPI Bus 2 of ESP32-S3)

#define TFT_CS         10   // IO10 = CSX   (Chip Select, active low)
#define TFT_DC         9    // IO09 = D/CX  (RS in KiCad — Data/Command select)
#define TFT_RST        21   // IO21 = RESX  (Reset, active low)
#define TFT_MOSI       11   // IO11 = SDA   (SPI MOSI — NV3007 naming for MOSI)
#define TFT_SCLK       12   // IO12 = SCL   (SPI SCLK — NV3007 naming for SCK)
// No TFT_MISO: NV3007 in 4-wire SPI mode has no dedicated MISO line.

// IO13 = TE (Tearing Effect) — vertical sync output from NV3007.
// Used to synchronize frame writes and prevent display tearing.
// Can be left unconnected during initial bringup.
#define TFT_TE         13   // IO13 = TE

// Backlight PWM control
#define TFT_BL         2    // IO02 = LCD_BRIGHT (PWM output)
#define TFT_BACKLIGHT_ON HIGH

// Native resolution of the ER-TFT2.79-1 / NV3007: 168 × 428 pixels.
// Swap WIDTH/HEIGHT here if mounting the display in landscape orientation.
#define TFT_WIDTH      168  // Short axis (columns)
#define TFT_HEIGHT     428  // Long axis  (rows)

// ── Navigation Buttons ────────────────────────────────────────────────────────
// IO40 (UP) is used as the primary Meshtastic button.
#define BUTTON_PIN              40   // IO40 = UP   (primary / main button)
#define BUTTON_PIN_ALT_UP       40   // IO40 = UP
#define BUTTON_PIN_ALT_DOWN     43   // TXD0 (GPIO43 in ESP32-S3) = DOWN
#define BUTTON_PIN_ALT_LEFT      1   // IO01 = LEFT
#define BUTTON_PIN_ALT_RIGHT    18   // IO18 = RIGHT

// ── Si4463 (second radio) — SPI Bus 2 — RESERVED ─────────────────────────────
// Pins are mapped here for reference. Uncomment when Si4463 support is added.
//
// #define SI4463_CS    14  // IO14 = CS2
// #define SI4463_SDN    4  // IO04 = SDN
// #define SI4463_IRQ    8  // IO08 = IRQ
// #define SI4463_SCK   15  // IO15 = SCK2
// #define SI4463_MOSI  16  // IO16 = MOSI2
// #define SI4463_MISO  17  // IO17 = MISO2

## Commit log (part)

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2026-02-04 feat(Hw):Init_Schematic
2026-02-06 feat(Hw):Update_Schematic
2026-02-09 feat(Hw):Init_BOM
2026-02-10 feat(Hw):Init_Chip_Change
2026-02-11 feat(Hw):Update_BOM
2026-02-18 feat(Hw):Init_Floorplan
2026-02-19 feat(Hw):Floorplan_Updated
2026-02-25 feat(Hw):Update_SI4463_Antenna
2026-02-25 Fix: Modify RF filter and DNP
2026-02-25 feat(Hw):Update_Floorplan
2026-02-26 feat(Hw):Update_Schematic_And_Init_Route
2026-02-27 feat(Hw):Update_Route
2026-02-27 feat(Hw):3D_Model_Added
2026-03-02 feat(Hw):Init_Schematic_Addon_Cerveza
2026-03-03 feat(Hw):Init_Floorplan_Add-On_Cerveza
2026-03-04 feat(Hw):Uppdate_Route
2026-03-04 feat(Hw):Update_Labels
2026-03-09 feat(Hw):Init_Route_Add_On_Cerveza
2026-03-09 feat(Hw):Init_Addon_Websec
2026-03-09 feat(Hw):Update_Schematic_And_Route_Addon_Cerveza
2026-03-13 feat(Hw):Update_Route_Websec
2026-03-18 feat(fw):Add Meshtastic submodule and update platform configuration
2026-03-19 feat(fw):Update ComponentsTable, platformio.ini, and variant.h for improved hardware definitions and configurations
2026-04-09 feat: 1s sample
2026-04-17 feat: add README for Tropicon 2026 project
2026-04-17 Remove redundant credits section in README
2026-04-17 add README for Tropicon 2026 firmware details
    Updated README with detailed firmware information and navigation instructions.
2026-04-17 add README for Tropicon 2026 firmware
    Removed detailed sections on navigation, Bluetooth connection, and flashing the device. Updated the introduction and added a link to the firmware repository.
2026-05-04 feat: Add CERN Open Hardware Licence v1.2
    Added CERN Open Hardware Licence v1.2 to the project.
